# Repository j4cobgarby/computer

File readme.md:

# My computer

## A Z80 computer that I've designed, but haven't made in real life yet

Here's the schematic:

The schematic shows 3 PIO chips to control various peripherals. In practice, I could add up to 5 more PIO chips, but since when I do implement this on a breadboard I will be able to place new components in easily, I left any extra PIO chips out of the schematic.

There are 4 EEPROM chips and 4 static RAM chips for a total of 512Kbits (64KB) of total memory. The various memory chips are enabled using a demultiplexer.

The output screen will be a 4x20 LCD display, alongside a 4-digit 7-segment display, but hobbytronics sells a really nice [VGA driver board](http://www.hobbytronics.co.uk/serial-vga) which I'm tempted to buy.

I haven't written any software for the processor yet.

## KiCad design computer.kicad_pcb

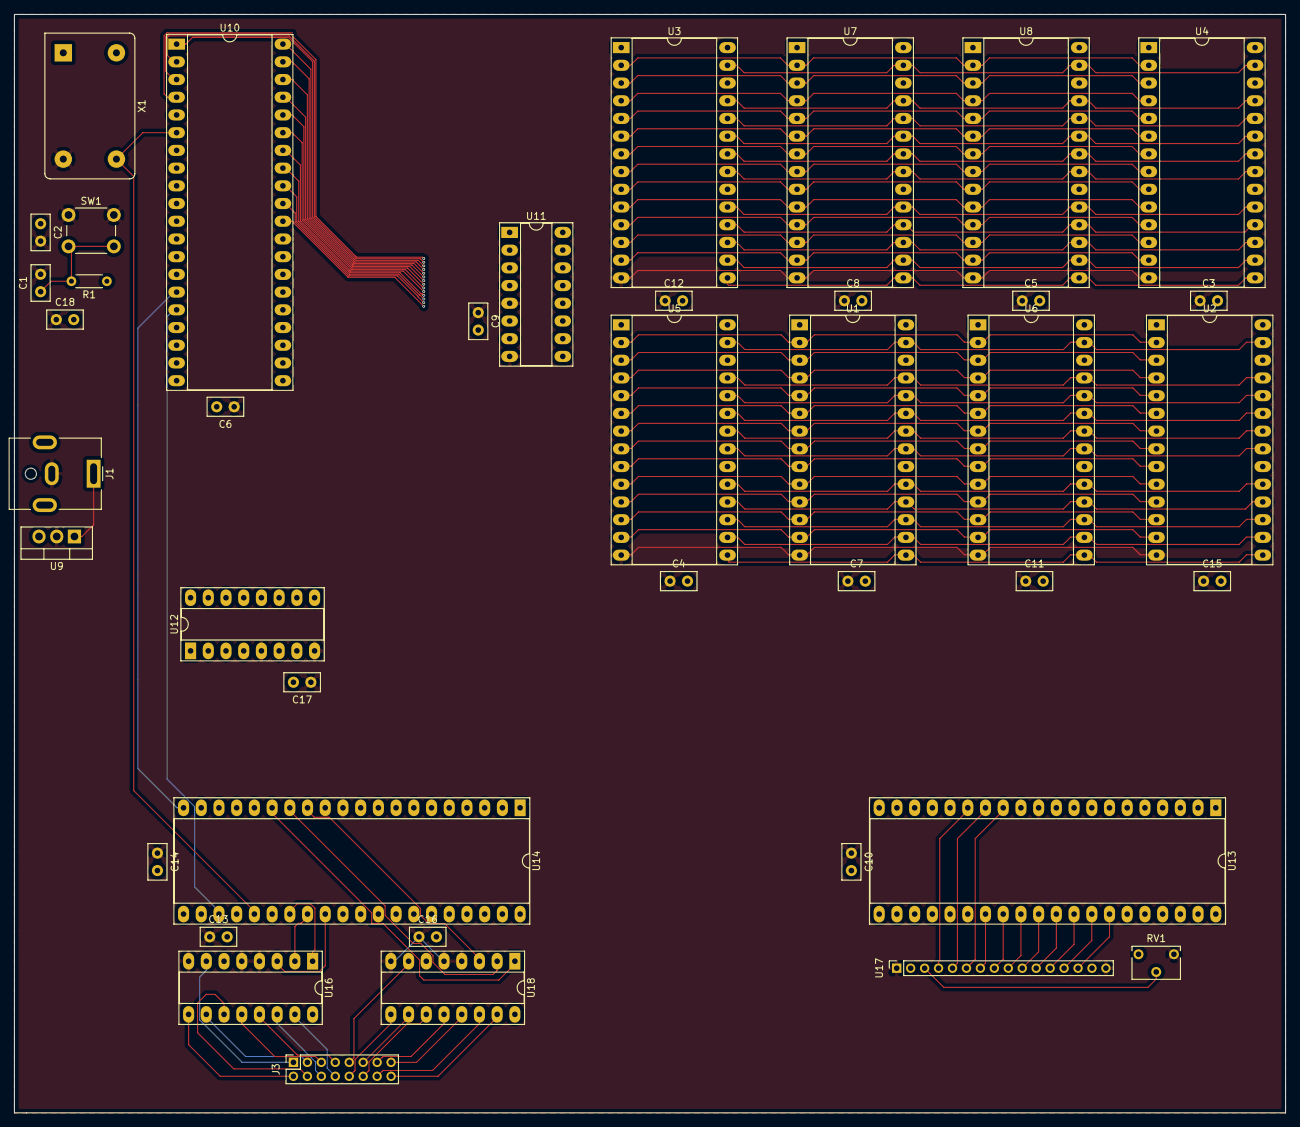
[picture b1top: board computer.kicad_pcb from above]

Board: 4 copper layers, 182.2 x 157.5 mm, 41 parts (0 on the bottom side), 79 nets.

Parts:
C1: 1u; C_Disc_D5.0mm_W2.5mm_P2.50mm
C2: 0.01uF; C_Disc_D5.0mm_W2.5mm_P2.50mm
C3, C4, C5, C6, C7, C8, C9, C10, C11, C12, C13, C14, C15, C16, C17, C18: 100nF; C_Disc_D5.0mm_W2.5mm_P2.50mm
J1: Jack-DC; BarrelJack_CUI_PJ-063AH_Horizontal
J3: Conn_02x08_Counter_Clockwise; PinSocket_2x08_P2.00mm_Vertical
R1: 1k; R_Axial_DIN0204_L3.6mm_D1.6mm_P5.08mm_Horizontal
RV1: 10k-20k; Potentiometer_Bourns_3266W_Vertical
SW1: SW_Push; SW_PUSH_6mm_H4.3mm
U1, U2, U5, U6: AS6C6264; DIP-28_W15.24mm_Socket_LongPads
U3, U4, U7, U8: AT28C64B; DIP-28_W15.24mm_Socket_LongPads
U9: L7805; TO-220-3_Vertical
U10: Z80CPU; DIP-40_W15.24mm_Socket_LongPads
U11, U12: CD74HCT138E; DIP-16_W7.62mm_Socket_LongPads
U13, U14: Z80_PIO; DIP-40_W15.24mm_Socket_LongPads
U16, U18: CD74HC238E; DIP-16_W7.62mm_Socket_LongPads
U17: NHD-0420H1Z; PinSocket_1x16_P2.00mm_Vertical
X1: ACO-8MHz; Oscillator_DIP-14_LargePads

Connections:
/CLK: U10.6, U13.25, U14.25, X1.8
/CPU_A0: U1.10, U2.10, U3.10, U4.10, U5.10, U6.10, U7.10, U8.10, U10.30, U13.6, U14.6
/CPU_A1: U1.9, U2.9, U3.9, U4.9, U5.9, U6.9, U7.9, U8.9, U10.31, U13.5, U14.5
/CPU_A2: U1.8, U2.8, U3.8, U4.8, U5.8, U6.8, U7.8, U8.8, U10.32, U12.1
/CPU_A3: U1.7, U2.7, U3.7, U4.7, U5.7, U6.7, U7.7, U8.7, U10.33, U12.2
/CPU_A4: U1.6, U2.6, U3.6, U4.6, U5.6, U6.6, U7.6, U8.6, U10.34, U12.3
/CPU_A5: U1.5, U2.5, U3.5, U4.5, U5.5, U6.5, U7.5, U8.5, U10.35
/CPU_A6: U1.4, U2.4, U3.4, U4.4, U5.4, U6.4, U7.4, U8.4, U10.36
/CPU_A7: U1.3, U2.3, U3.3, U4.3, U5.3, U6.3, U7.3, U8.3, U10.37
/CPU_A8: U1.25, U2.25, U3.25, U4.25, U5.25, U6.25, U7.25, U8.25, U10.38
/CPU_A9: U1.24, U2.24, U3.24, U4.24, U5.24, U6.24, U7.24, U8.24, U10.39
/CPU_A10: U1.21, U2.21, U3.21, U4.21, U5.21, U6.21, U7.21, U8.21, U10.40
/CPU_A11: U1.23, U2.23, U3.23, U4.23, U5.23, U6.23, U7.23, U8.23, U10.1
/CPU_A12: U1.2, U2.2, U3.2, U4.2, U5.2, U6.2, U7.2, U8.2, U10.2
/CPU_A13: U10.3, U11.1
/CPU_A14: U10.4, U11.2
/CPU_A15: U10.5, U11.3
/CPU_INT: U10.16, U13.23, U14.23
/CPU_IORQ: U10.20, U13.4, U14.4
/CPU_M1: U10.27, U13.37, U14.37
/CPU_MREQ: U10.19, U11.4
/CPU_RD: U1.22, U2.22, U3.22, U4.22, U5.22, U6.22, U7.22, U8.22, U10.21, U13.35, U14.35
/CPU_WR: U1.27, U2.27, U3.27, U4.27, U5.27, U6.27, U7.27, U8.27, U10.22
/D0: U1.11, U2.11, U3.11, U4.11, U5.11, U6.11, U7.11, U8.11, U10.14, U13.19, U14.19
/D1: U1.12, U2.12, U3.12, U4.12, U5.12, U6.12, U7.12, U8.12, U10.15, U13.20, U14.20
/D2: U1.13, U2.13, U3.13, U4.13, U5.13, U6.13, U7.13, U8.13, U10.12, U13.1, U14.1
/D3: U1.15, U2.15, U3.15, U4.15, U5.15, U6.15, U7.15, U8.15, U10.8, U13.40, U14.40
/D4: U1.16, U2.16, U3.16, U4.16, U5.16, U6.16, U7.16, U8.16, U10.7, U13.39, U14.39
/D5: U1.17, U2.17, U3.17, U4.17, U5.17, U6.17, U7.17, U8.17, U10.9, U13.38, U14.38
/D6: U1.18, U2.18, U3.18, U4.18, U5.18, U6.18, U7.18, U8.18, U10.10, U13.3, U14.3
/D7: U1.19, U2.19, U3.19, U4.19, U5.19, U6.19, U7.19, U8.19, U10.13, U13.2, U14.2
GND: C1.2, C2.2, C3.1, C4.1, C5.1, C6.1, C7.1, C8.1, C9.1, C10.1, C11.1, C12.1, C13.1, C14.1, C15.1, C16.1, C17.1, C18.1, J1.2, RV1.1, SW1.1, U1.14, U2.14, U3.14, U4.14, U5.14, U6.14, U7.14, U8.14, U9.2, U10.29, U11.5, U11.8, U12.5, U12.8, U13.11, U14.11, U16.4, U16.5, U16.8, U17.1, U17.16, U18.4, U18.5, U18.8, X1.7
unnamed: C1.1, R1.2, SW1.2, U10.26
unnamed: J1.1, U9.1
unnamed: RV1.2, U17.3
unnamed: U1.20, U11.10
unnamed: U2.20, U11.7
unnamed: U6.20, U11.9
unnamed: U5.20, U11.11
unnamed: U4.20, U11.12
unnamed: U3.20, U11.13
unnamed: U8.20, U11.14
unnamed: U7.20, U11.15
unnamed: U12.13, U14.36
unnamed: U12.15, U13.36
unnamed: U13.13, U17.6
unnamed: U13.14, U17.5
unnamed: U13.15, U17.4
unnamed: U13.27, U17.7
unnamed: U13.28, U17.8
unnamed: U13.29, U17.9
unnamed: U13.30, U17.10
unnamed: U13.31, U17.11
unnamed: U13.32, U17.12
unnamed: U13.33, U17.13
unnamed: U13.34, U17.14
unnamed: U14.13, U18.3
unnamed: U14.14, U18.2
unnamed: U14.15, U18.1
unnamed: U14.27, U16.1
unnamed: U14.28, U16.2
unnamed: U14.29, U16.3
VCC: C2.1, C3.2, C4.2, C5.2, C6.2, C7.2, C8.2, C9.2, C10.2, C11.2, C12.2, C13.2, C14.2, C15.2, C16.2, C17.2, C18.2, R1.1, RV1.3, U1.26, U1.28, U2.26, U2.28, U3.28, U4.28, U5.26, U5.28, U6.26, U6.28, U7.28, U8.28, U9.3, U10.11, U11.6, U11.16, U12.6, U12.16, U13.26, U14.26, U16.6, U16.16, U17.2, U17.15, U18.6, U18.16, X1.14
kbd_in0: J3.8, U16.15
kbd_in1: J3.7, U16.13
kbd_in2: J3.6, U16.14
kbd_in3: J3.5, U16.12
kbd_in4: J3.4, U16.11
kbd_in5: J3.3, U16.10
kbd_in6: J3.2, U16.9
kbd_in7: J3.1, U16.7
kbd_out0: J3.16, U18.15
kbd_out1: J3.15, U18.13
kbd_out2: J3.14, U18.14
kbd_out3: J3.13, U18.12
kbd_out4: J3.12, U18.11
kbd_out5: J3.11, U18.10
kbd_out6: J3.10, U18.9
kbd_out7: J3.9, U18.7

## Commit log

2019-02-13 initial
2019-02-14 aaaaaaaa
2019-02-19 media
